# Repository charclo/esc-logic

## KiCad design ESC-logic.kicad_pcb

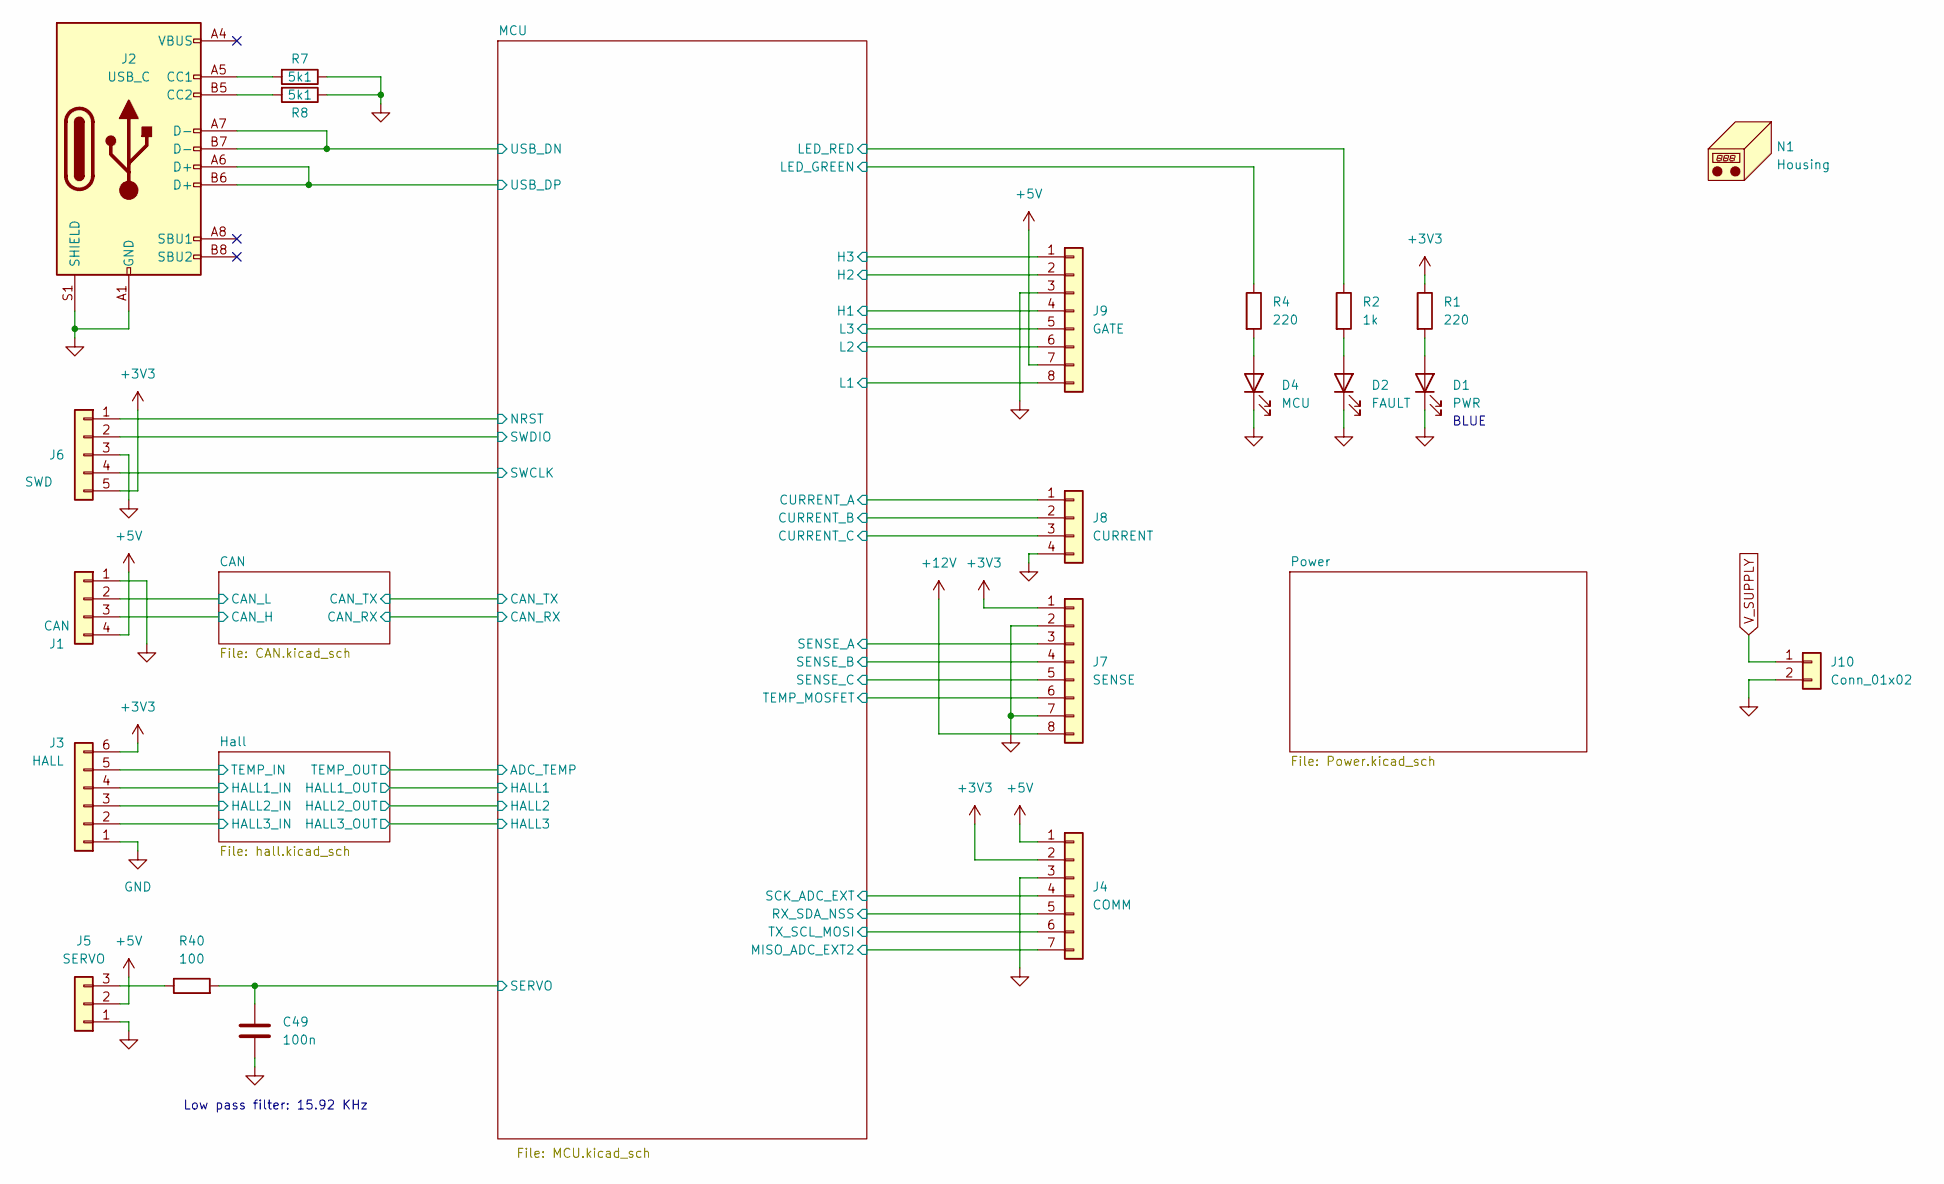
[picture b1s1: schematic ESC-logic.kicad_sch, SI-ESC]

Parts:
C49: 100n; C_0805_2012Metric; LCSC C49678
D1: PWR; LED_0805_2012Metric; LCSC C965817
D2: FAULT; LED_0805_2012Metric; LCSC C131244
D4: MCU; LED_0805_2012Metric; LCSC C965816
J1: CAN; JST_PH_S4B-PH-K_1x04_P2.00mm_Horizontal
J2: USB_C; USB_C_Receptacle_HRO_TYPE-C-31-M-12; LCSC C709357
J3: HALL; JST_PH_S6B-PH-K_1x06_P2.00mm_Horizontal
J4: COMM; JST_PH_S7B-PH-K_1x07_P2.00mm_Horizontal
J5: SERVO; JST_PH_S3B-PH-K_1x03_P2.00mm_Horizontal
J6: SWD; JST_PH_S5B-PH-K_1x05_P2.00mm_Horizontal
J7: SENSE; PinHeader_2x04_P2.54mm_Vertical
J8: CURRENT; PinHeader_2x02_P2.54mm_Vertical
J9: GATE; PinHeader_2x04_P2.54mm_Vertical
J10: Conn_01x02; PinHeader_1x02_P2.54mm_Vertical
N1: Housing; KiCad-Logo2_5mm_SilkScreen
R1, R4: 220; R_0805_2012Metric; LCSC C407469
R2: 1k; R_0805_2012Metric; LCSC C79496
R7, R8: 5k1; R_0805_2012Metric; LCSC C84375
R40: 100; R_0805_2012Metric; LCSC C105577

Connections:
+5V: J1.4, J4.1, J5.2, J9.7; also elsewhere on the board
/CAN/CAN_H: J1.3; also elsewhere on the board
/CAN/CAN_L: J1.2; also elsewhere on the board
/Hall/HALL1_IN: J3.4; also elsewhere on the board
/Hall/HALL2_IN: J3.3; also elsewhere on the board
/Hall/HALL3_IN: J3.2; also elsewhere on the board
/Hall/TEMP_IN: J3.5; also elsewhere on the board
/MCU/CURRENT_A: J8.1; also elsewhere on the board
/MCU/CURRENT_B: J8.2; also elsewhere on the board
/MCU/CURRENT_C: J8.3; also elsewhere on the board
/MCU/H1: J9.4; also elsewhere on the board
/MCU/H2: J9.2; also elsewhere on the board
/MCU/H3: J9.1; also elsewhere on the board
/MCU/L1: J9.8; also elsewhere on the board
/MCU/L2: J9.6; also elsewhere on the board
/MCU/L3: J9.5; also elsewhere on the board
/MCU/LED_GREEN: R4.1; also elsewhere on the board
/MCU/LED_RED: R2.1; also elsewhere on the board
/MCU/MISO_ADC_EXT2: J4.7; also elsewhere on the board
/MCU/NRST: J6.1; also elsewhere on the board
/MCU/RX_SDA_NSS: J4.5; also elsewhere on the board
/MCU/SCK_ADC_EXT: J4.4; also elsewhere on the board
/MCU/SENSE_A: J7.3; also elsewhere on the board
/MCU/SENSE_B: J7.4; also elsewhere on the board
/MCU/SENSE_C: J7.5; also elsewhere on the board
/MCU/SERVO: C49.1, R40.2; also elsewhere on the board
/MCU/SWCLK: J6.4; also elsewhere on the board
/MCU/SWDIO: J6.2; also elsewhere on the board
/MCU/TEMP_MOSFET: J7.6; also elsewhere on the board
/MCU/TX_SCL_MOSI: J4.6; also elsewhere on the board
/MCU/USB_DN: J2.A7 (D-), J2.B7 (D-); also elsewhere on the board
/MCU/USB_DP: J2.A6 (D+), J2.B6 (D+); also elsewhere on the board
unnamed: D1.2 (A), R1.2
unnamed: D2.2 (A), R2.2
unnamed: D4.2 (A), R4.2
unnamed: J2.A5 (CC1), R7.2
unnamed: J2.B5 (CC2), R8.2
unnamed: J5.3, R40.1
V_SUPPLY: J10.1; also elsewhere on the board

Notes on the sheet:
Low pass filter: 15.92 KHz
BLUE

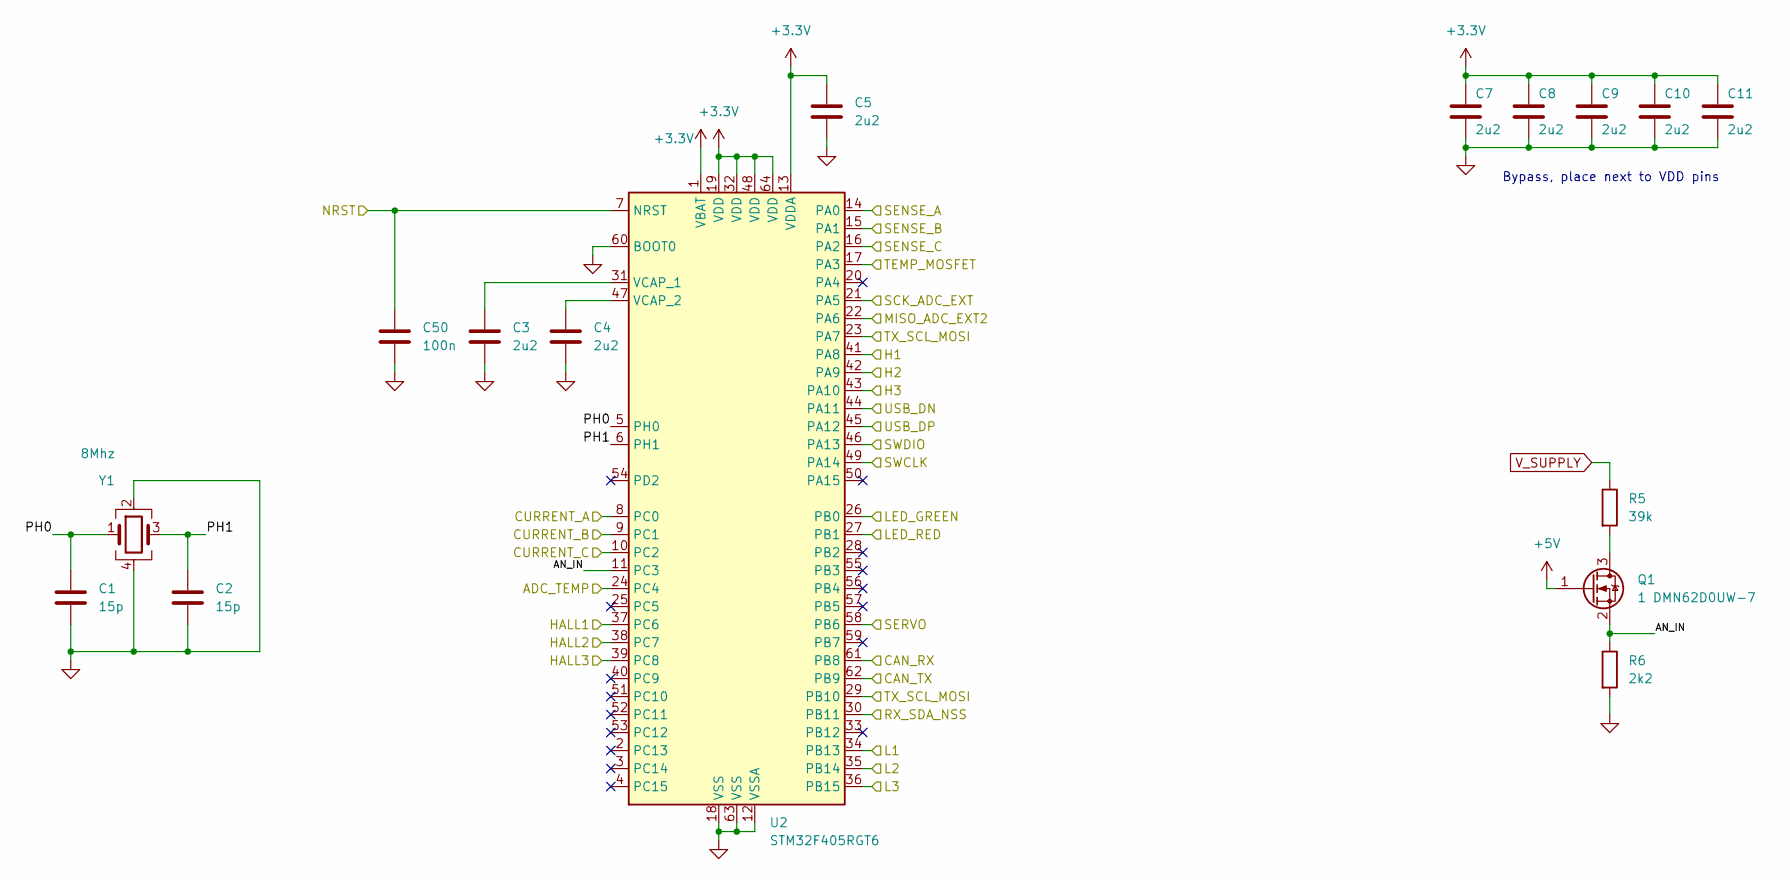
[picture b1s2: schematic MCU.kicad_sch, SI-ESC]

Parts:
C1, C2: 15p; C_0805_2012Metric; LCSC C107110
C3, C4, C5, C7, C8, C9, C10, C11: 2u2; C_0805_2012Metric; LCSC C319190
C50: 100n; C_0805_2012Metric; LCSC C49678
Q1: 1 DMN62D0UW-7; SOT-323_SC-70; LCSC C156342
R5: 39k; R_0805_2012Metric; LCSC C113306
R6: 2k2; R_0805_2012Metric; LCSC C2907234
U2: STM32F405RGT6; LQFP-64_10x10mm_P0.5mm; Manufacture Part Number STM32F405RGT6; LCSC C15742
Y1: 8Mhz; Crystal_SMD_3225-4Pin_3.2x2.5mm; LCSC C2924619

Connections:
+5V: Q1.1 (G); also elsewhere on the board
/CAN/CAN_RX: U2.61 (PB8); also elsewhere on the board
/CAN/CAN_TX: U2.62 (PB9); also elsewhere on the board
/Hall/HALL1_IN: U2.37 (PC6); also elsewhere on the board
/Hall/HALL2_IN: U2.38 (PC7); also elsewhere on the board
/Hall/HALL3_IN: U2.39 (PC8); also elsewhere on the board
/Hall/TEMP_IN: U2.24 (PC4); also elsewhere on the board
/MCU/AN_IN: Q1.2 (S), R6.1, U2.11 (PC3)
/MCU/CURRENT_A: U2.8 (PC0); also elsewhere on the board
/MCU/CURRENT_B: U2.9 (PC1); also elsewhere on the board
/MCU/CURRENT_C: U2.10 (PC2); also elsewhere on the board
/MCU/H1: U2.41 (PA8); also elsewhere on the board
/MCU/H2: U2.42 (PA9); also elsewhere on the board
/MCU/H3: U2.43 (PA10); also elsewhere on the board
/MCU/L1: U2.34 (PB13); also elsewhere on the board
/MCU/L2: U2.35 (PB14); also elsewhere on the board
/MCU/L3: U2.36 (PB15); also elsewhere on the board
/MCU/LED_GREEN: U2.26 (PB0); also elsewhere on the board
/MCU/LED_RED: U2.27 (PB1); also elsewhere on the board
/MCU/MISO_ADC_EXT2: U2.22 (PA6); also elsewhere on the board
/MCU/NRST: C50.1, U2.7 (NRST); also elsewhere on the board
/MCU/PH0: C1.1, U2.5 (PH0), Y1.1
/MCU/PH1: C2.1, U2.6 (PH1), Y1.3
/MCU/RX_SDA_NSS: U2.30 (PB11); also elsewhere on the board
/MCU/SCK_ADC_EXT: U2.21 (PA5); also elsewhere on the board
/MCU/SENSE_A: U2.14 (PA0); also elsewhere on the board
/MCU/SENSE_B: U2.15 (PA1); also elsewhere on the board
/MCU/SENSE_C: U2.16 (PA2); also elsewhere on the board
/MCU/SERVO: U2.58 (PB6); also elsewhere on the board
/MCU/SWCLK: U2.49 (PA14); also elsewhere on the board
/MCU/SWDIO: U2.46 (PA13); also elsewhere on the board
/MCU/TEMP_MOSFET: U2.17 (PA3); also elsewhere on the board
/MCU/TX_SCL_MOSI: U2.23 (PA7), U2.29 (PB10); also elsewhere on the board
/MCU/USB_DN: U2.44 (PA11); also elsewhere on the board
/MCU/USB_DP: U2.45 (PA12); also elsewhere on the board
unnamed: Q1.3 (D), R5.2
unnamed: C3.1, U2.31 (VCAP_1)
unnamed: C4.1, U2.47 (VCAP_2)
V_SUPPLY: R5.1; also elsewhere on the board

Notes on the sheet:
Bypass, place next to VDD pins

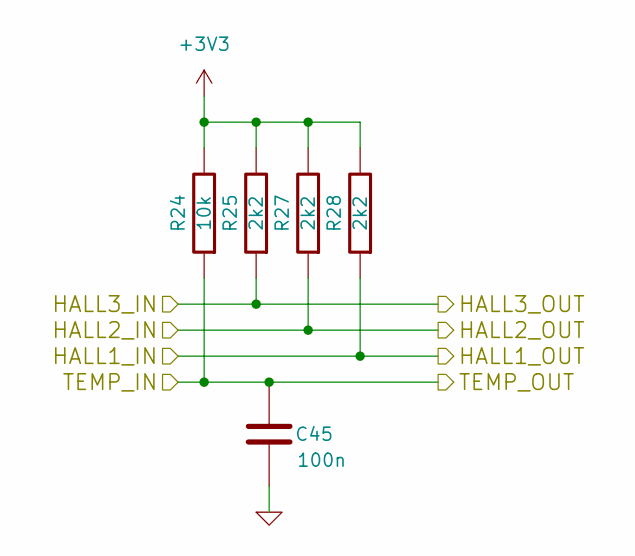
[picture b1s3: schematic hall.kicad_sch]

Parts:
C45: 100n; C_0805_2012Metric; LCSC C49678
R24: 10k; R_0805_2012Metric; LCSC C84376
R25, R27, R28: 2k2; R_0805_2012Metric; LCSC C2907234

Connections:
/Hall/HALL1_IN: R28.1; also elsewhere on the board
/Hall/HALL2_IN: R27.1; also elsewhere on the board
/Hall/HALL3_IN: R25.1; also elsewhere on the board
/Hall/TEMP_IN: C45.2, R24.1; also elsewhere on the board

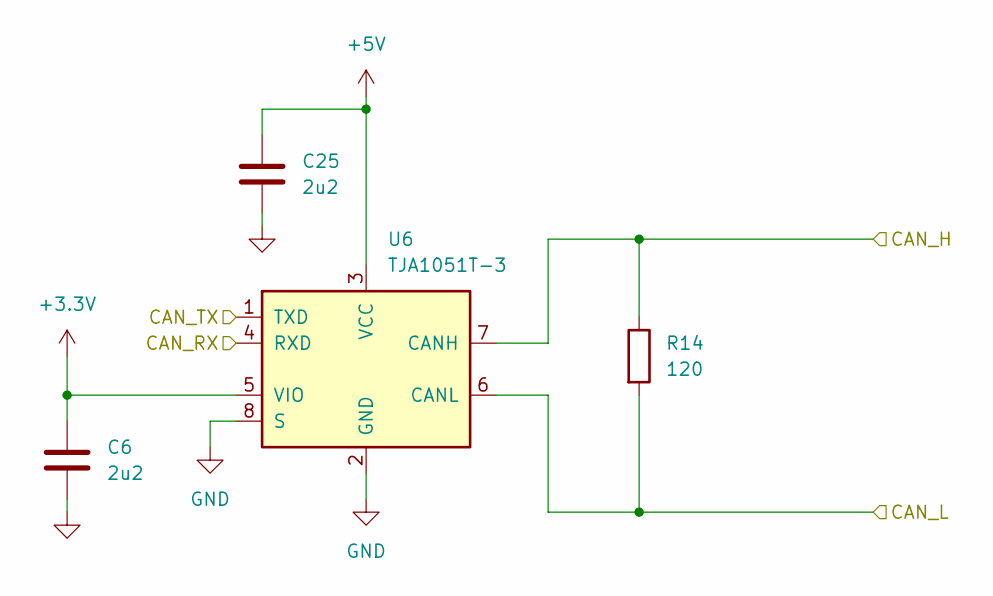
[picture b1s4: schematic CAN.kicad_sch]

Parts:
C6, C25: 2u2; C_0805_2012Metric; LCSC C319190
R14: 120; R_0805_2012Metric; LCSC C114245
U6: TJA1051T-3; SOIC-8_3.9x4.9mm_P1.27mm; Manufacture Part Number TJA1051T/3,118; LCSC C58988

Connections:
+5V: C25.1, U6.3 (VCC); also elsewhere on the board
/CAN/CAN_H: R14.1, U6.7 (CANH); also elsewhere on the board
/CAN/CAN_L: R14.2, U6.6 (CANL); also elsewhere on the board
/CAN/CAN_RX: U6.4 (RXD); also elsewhere on the board
/CAN/CAN_TX: U6.1 (TXD); also elsewhere on the board

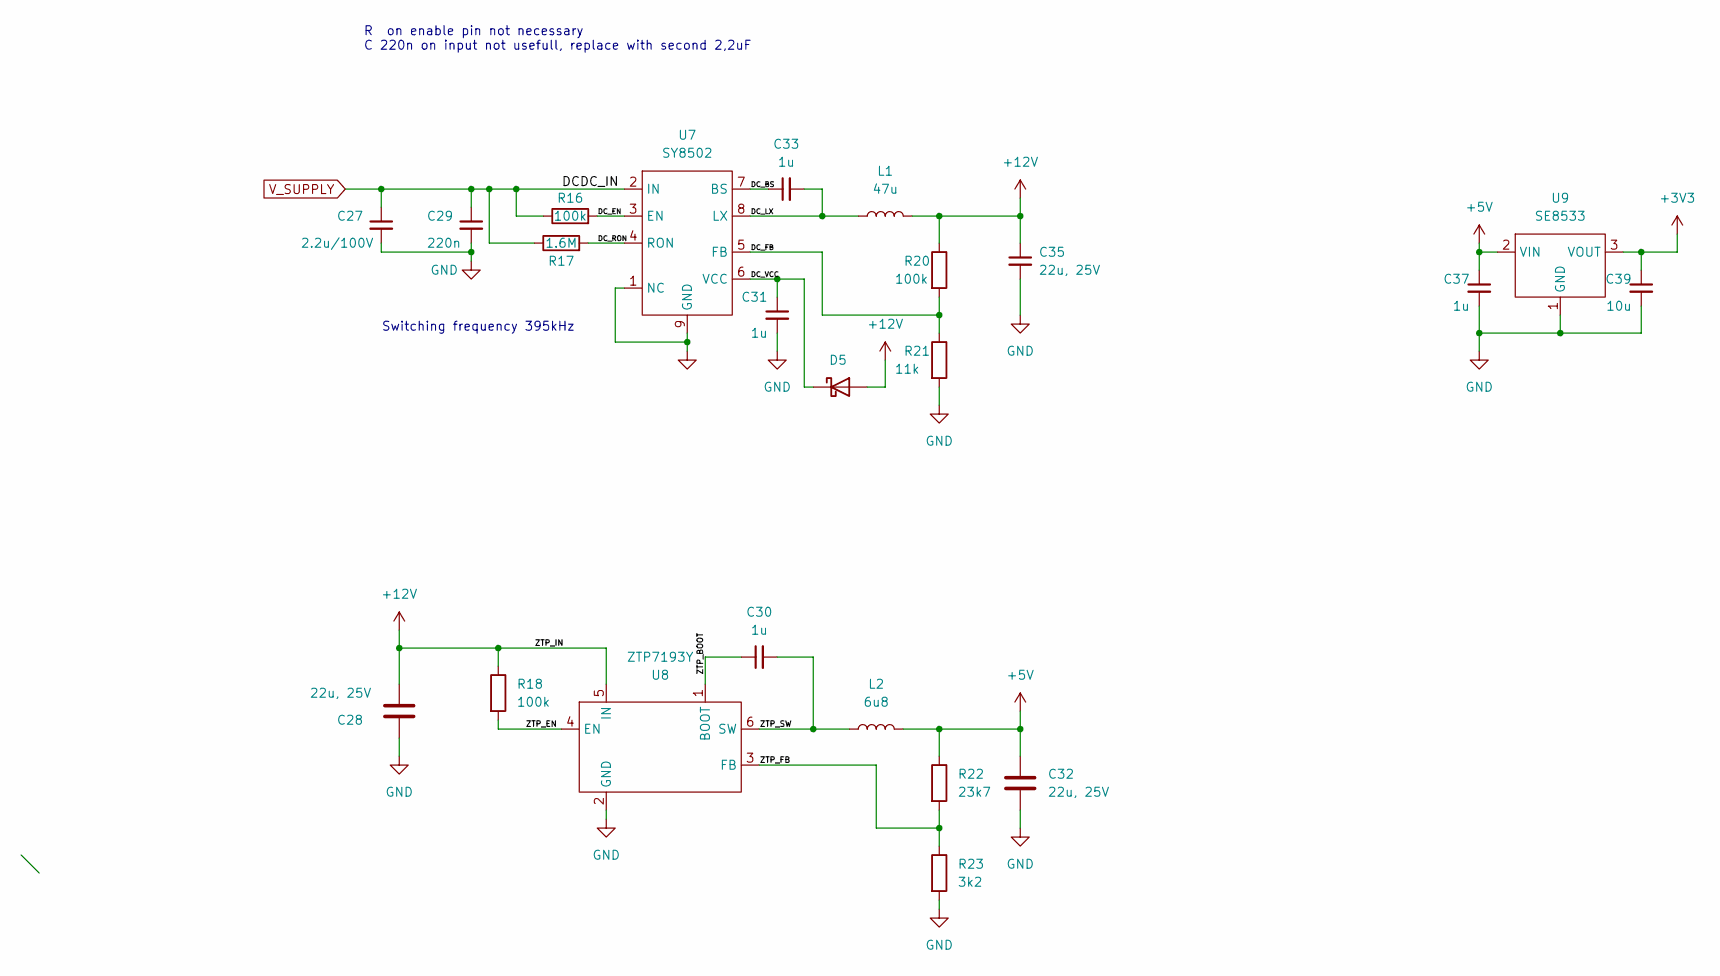
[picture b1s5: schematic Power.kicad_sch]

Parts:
C27: 2.2u/100V; C_1210_3225Metric; LCSC C412614
C28, C32, C35: 22u, 25V; C_0805_2012Metric; LCSC C45783
C29: 220n; C_0805_2012Metric; LCSC C729464
C30, C31, C33, C37: 1u; C_0805_2012Metric; LCSC C319195
C39: 10u; C_0805_2012Metric; LCSC C15850
D5: D_Schottky; D_SOD-123; LCSC C2890313
L1: 47u; L_Taiyo-Yuden_NR-80xx; LCSC C206268
L2: 6u8; L_Taiyo-Yuden_NR-40xx; LCSC C326302
R16, R18, R20: 100k; R_0805_2012Metric; LCSC C180850
R17: 1.6M; R_0805_2012Metric; LCSC C413343
R21: 11k; R_0805_2012Metric; LCSC C136917
R22: 23k7; R_0805_2012Metric; LCSC C2930184
R23: 3k2; R_0805_2012Metric
U7: SY8502; HSOP-8-1EP_3.9x4.9mm_P1.27mm_EP2.41x3.1mm; LCSC C87752
U8: ZTP7193Y; TSOT-23-6; LCSC C481280
U9: SE8533; SOT-89-3; LCSC C115013

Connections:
+5V: C32.1, C37.1, L2.2, R22.1, U9.2 (VIN); also elsewhere on the board
/Power/DC_BS: C33.1, U7.7 (BS)
/Power/DC_EN: R16.2, U7.3 (EN)
/Power/DC_FB: R20.2, R21.1, U7.5 (FB)
/Power/DC_LX: C33.2, L1.1, U7.8 (LX)
/Power/DC_RON: R17.2, U7.4 (RON)
/Power/DC_VCC: C31.1, D5.1 (K), U7.6 (VCC)
/Power/ZTP_BOOT: C30.1, U8.1 (BOOT)
/Power/ZTP_EN: R18.2, U8.4 (EN)
/Power/ZTP_FB: R22.2, R23.1, U8.3 (FB)
/Power/ZTP_SW: C30.2, L2.1, U8.6 (SW)
V_SUPPLY: C27.1, C29.1, R16.1, R17.1, U7.2 (IN); also elsewhere on the board

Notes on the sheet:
R on enable pin not necessary C 220n on input not usefull, replace with second 2,2uF
Switching frequency 395kHz

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
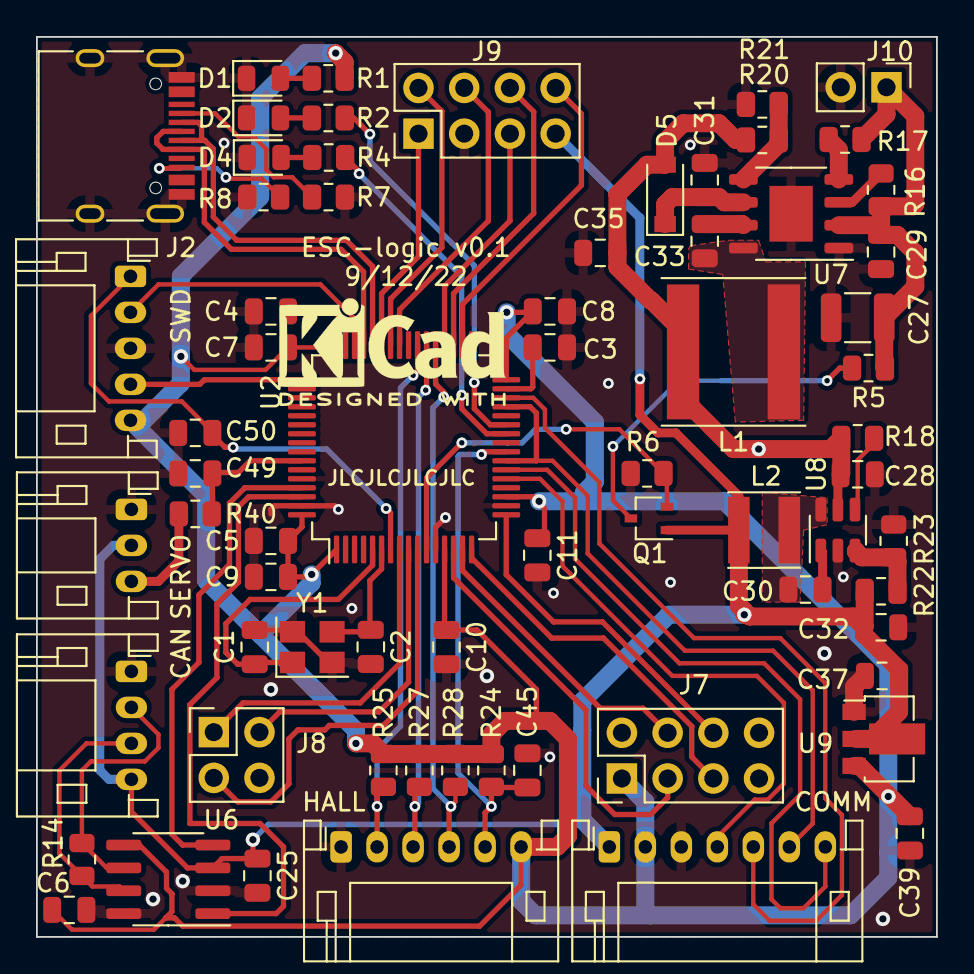
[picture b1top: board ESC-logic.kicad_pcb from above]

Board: 4 copper layers, 50.0 x 50.0 mm, 69 parts (0 on the bottom side), 60 nets.

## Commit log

2022-12-05 Changed jst connectors
2022-12-09 v0.1 finished
2023-11-04 what changed?
